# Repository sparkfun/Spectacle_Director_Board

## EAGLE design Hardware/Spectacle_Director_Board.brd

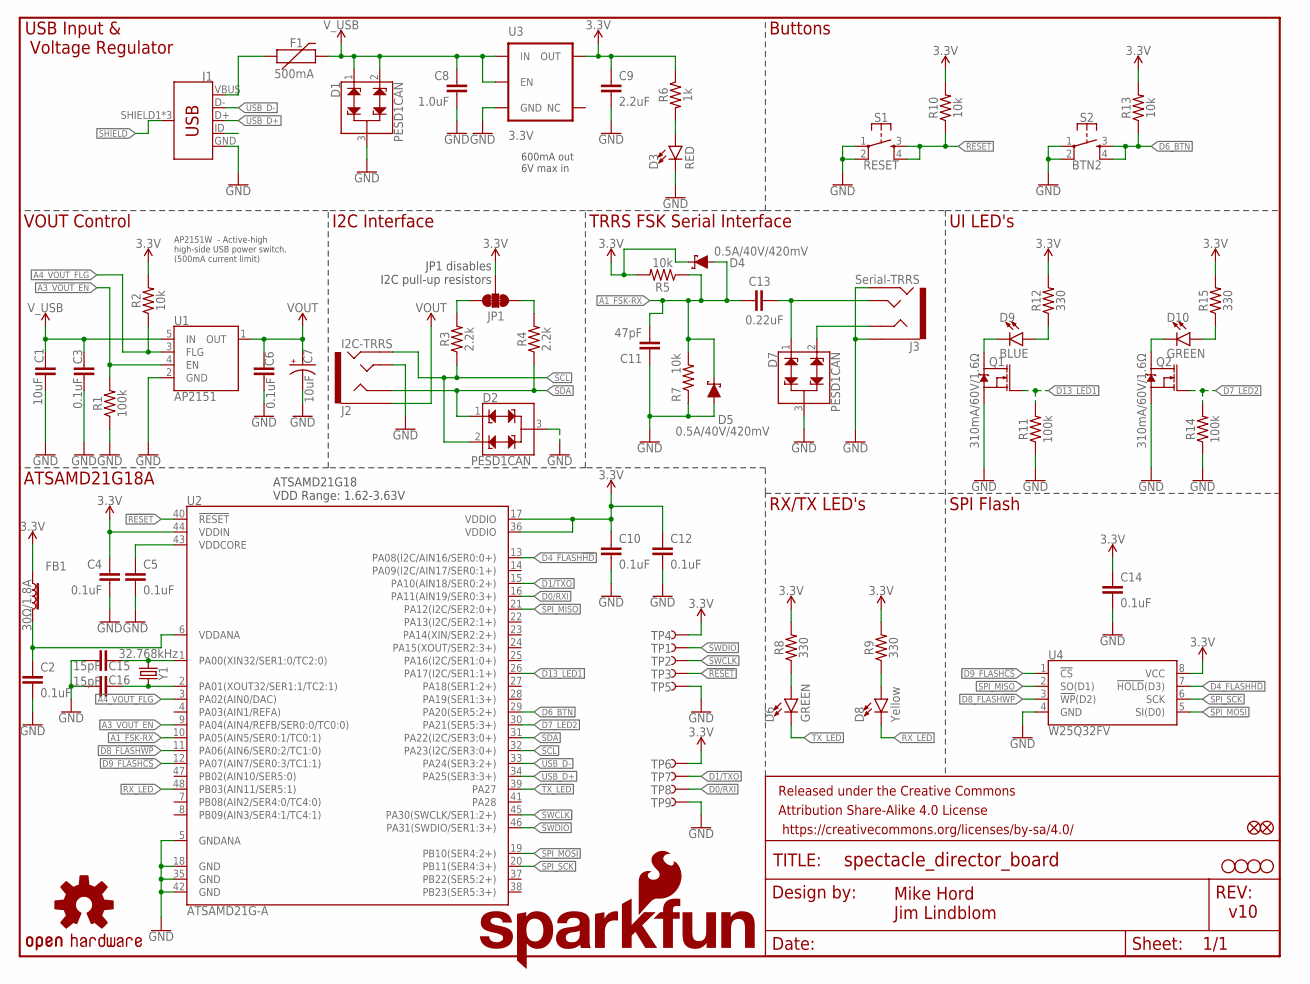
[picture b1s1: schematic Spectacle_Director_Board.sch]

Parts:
C1: 10uF; 0805
C2, C3, C4, C5, C6, C10, C12, C14: 0.1uF; 0603
C7: 10uF; EIA3216
C8: 1.0uF; 0805
C9: 2.2uF; 0603
C11: 47pF; 0603
C13: 0.22uF; 0603
C15, C16: 15pF; 0603
D1, D2, D7: PESD1CAN; SOT23-3
D3: RED; LED-0603
D4, D5: 0.5A/40V/420mV; SOD-323
D6, D10: GREEN; LED-0603
D8: Yellow; LED-0603
D9: BLUE; LED-0603
F1: 500mA; PTC-1206
FB1: 30Ω/1.8A; 0603
FD1, FD2: FIDUCIALUFIDUCIAL; FIDUCIAL-MICRO
FRAME1: FRAME-LETTER; CREATIVE_COMMONS
H1, H2, H3, H4: STAND-OFF
J1: USB_MICRO-B_FEMALE-SMT; USB-B-MICRO-SMD
J2: I2C-TRRS; AUDIO_JACK_3.5MM_TRRS_SMD_RA
J3: Serial-TRRS; AUDIO_JACK_3.5MM_TRRS_SMD_RA
JP1: JUMPER-SMT_3_2-NC_TRACE_NO-SILK; SMT-JUMPER_3_2-NC_TRACE_NO-SILK
LOGO1: OSHW-LOGOMINI; OSHW-LOGO-MINI
LOGO2: SFE_LOGO_NAME.2_INCH; SFE_LOGO_NAME_.2
LOGO3: SFE_LOGO_FLAME.1COP; SFE_LOGO_FLAME_COPPER_.1
Q1, Q2: 310mA/60V/1.6Ω; SOT323
R1, R11, R14: 100k; 0603
R2, R5, R7, R10, R13: 10k; 0603
R3, R4: 2.2k; 0603
R6: 1k; 0603
R8, R9, R12, R15: 330; 0603
S1: RESET; TACTILE_SWITCH_SMD_4.6X2.8MM
S2: BTN2; TACTILE_SWITCH_SMD_4.6X2.8MM
TP1: TP-SWDIO; PAD.03X.05
TP2: TP-SWCLK; PAD.03X.05
TP3: TP-!RESET!; PAD.03X.05
TP4: TP-3.3V; PAD.03X.05
TP5, TP6, TP7, TP8, TP9: TP-GND; PAD.03X.05
U1: AP2151; SOT23-5
U2: ATSAMD21G-A; TQFP-48
U3: 3.3V; SOT23-5
U4: W25Q32FV; SOIC-8
Y1: 32.768kHz; CRYSTAL-SMD-3.2X1.5MM

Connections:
3.3V: C4.1, C9.1, C10.1, C12.1, C14.1, D4.C, FB1.1, JP1.2, R2.2, R5.2, R6.1, R8.2, R9.2, R10.2, R12.2, R13.2, R15.2, TP4.P$1, TP6.P$1, U2.17 (VDDIO), U2.36 (VDDIO), U2.44 (VDDIN), U3.5 (OUT), U4.8 (VCC)
!RESET: R10.1, S1.3, S1.4, TP3.P$1, U2.40 (!RESET!)
A1_FSK-RX: C11.2, C13.1, D4.A, D5.C, R5.1, R7.2, U2.10 (PA05(AIN5/SER0:1/TC0:1))
A3_VOUT_EN: R1.2, U1.4 (EN), U2.9 (PA04(AIN4/REFB/SER0:0/TC0:0))
A4_VOUT_FLG: R2.1, U1.3 (FLG), U2.3 (PA02(AIN0/DAC))
D0/RXI: TP8.P$1, U2.16 (PA11(AIN19/SER0:3+))
D1/TXO: TP7.P$1, U2.15 (PA10(AIN18/SER0:2+))
D4_FLASH!HD!: U2.13 (PA08(I2C/AIN16/SER0:0+)), U4.7 (!HOLD!(D3))
D6_BTN: R13.1, S2.3, S2.4, U2.29 (PA20(SER5:2+))
D7_LED2: Q2.1 (G), R14.2, U2.30 (PA21(SER5:3+))
D8_FLASH!WP!: U2.11 (PA06(AIN6/SER0:2/TC1:0)), U4.3 (!WP!(D2))
D9_FLASH!CS!: U2.12 (PA07(AIN7/SER0:3/TC1:1)), U4.1 (!CS!)
D13_LED1: Q1.1 (G), R11.2, U2.26 (PA17(I2C/SER1:1+))
GND: C1.2, C2.2, C3.2, C4.2, C5.2, C6.2, C7.-, C8.2, C9.2, C10.2, C11.1, C12.2, C14.2, C15.1, C16.1, D1.3, D2.3, D3.C, D5.A, D7.3, J1.GND, J2.TIP, J3.EARTH, J3.RING2, Q1.2 (S), Q2.2 (S), R1.1, R7.1, R11.1, R14.1, S1.1, S1.2, S2.1, S2.2, TP5.P$1, TP9.P$1, U1.2 (GND), U2.5 (GNDANA), U2.18 (GND), U2.35 (GND), U2.42 (GND), U3.2 (GND), U4.4 (GND)
unnamed: D10.A, R15.1
unnamed: D3.A, R6.2
unnamed: C15.2, U2.1 (PA00(XIN32/SER1:0/TC2:0)), Y1.P$2 (2)
unnamed: JP1.3, R3.2
unnamed: JP1.1, R4.2
unnamed: C16.2, U2.2 (PA01(XOUT32/SER1:1/TC2:1)), Y1.P$1 (1)
unnamed: D10.C, Q2.3 (D)
unnamed: D9.A, R12.1
unnamed: D9.C, Q1.3 (D)
unnamed: D6.A, R8.1
unnamed: D8.A, R9.1
RING1-RIGHT: D7.2, J3.RING1
RX_LED: D8.C, U2.48 (PB03(AIN11/SER5:1))
SCL: D2.2, J2.RING2, R3.1, U2.32 (PA23(I2C/SER3:0+))
SDA: D2.1, J2.RING1, R4.1, U2.31 (PA22(I2C/SER3:0+))
SHIELD: J1.SHIELD1 (SHIELD), J1.SHIELD2 (SHIELD), J1.SHIELD3 (SHIELD)
SPI_MISO: U2.21 (PA12(I2C/SER2:0+)), U4.2 (SO(D1))
SPI_MOSI: U2.19 (PB10(SER4:2+)), U4.5 (SI(D0))
SPI_SCK: U2.20 (PB11(SER4:3+)), U4.6 (SCK)
SWCLK: TP2.P$1, U2.45 (PA30(SWCLK/SER1:2+))
SWDIO: TP1.P$1, U2.46 (PA31(SWDIO/SER1:3+))
TIP-LEFT: C13.2, D7.1, J3.TIP
TX_LED: D6.C, U2.39 (PA27)
USB_D+: J1.D+, U2.34 (PA25(SER3:3+))
USB_D-: J1.D-, U2.33 (PA24(SER3:2+))
USB_ID: J1.ID
VDDANA: C2.1, FB1.2, U2.6 (VDDANA)
VDDCORE: C5.1, U2.43 (VDDCORE)
VOUT: C6.1, C7.+, J2.EARTH, U1.1 (OUT)
VUSB: F1.1, J1.VBUS
V_USB: C1.1, C3.1, C8.1, D1.1, D1.2, F1.2, U1.5 (IN), U3.1 (IN), U3.3 (EN)

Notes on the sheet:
600mA out 6V max in
v10
Mike Hord Jim Lindblom
JP1 disables I2C pull-up resistors
ATSAMD21G18 VDD Range: 1.62-3.63V
USB Input & Voltage Regulator
Buttons
SPI Flash
ATSAMD21G18A
RX/TX LED's
UI LED's
I2C Interface
TRRS FSK Serial Interface
VOUT Control
AP2151W - Active-high high-side USB power switch. (500mA current limit)

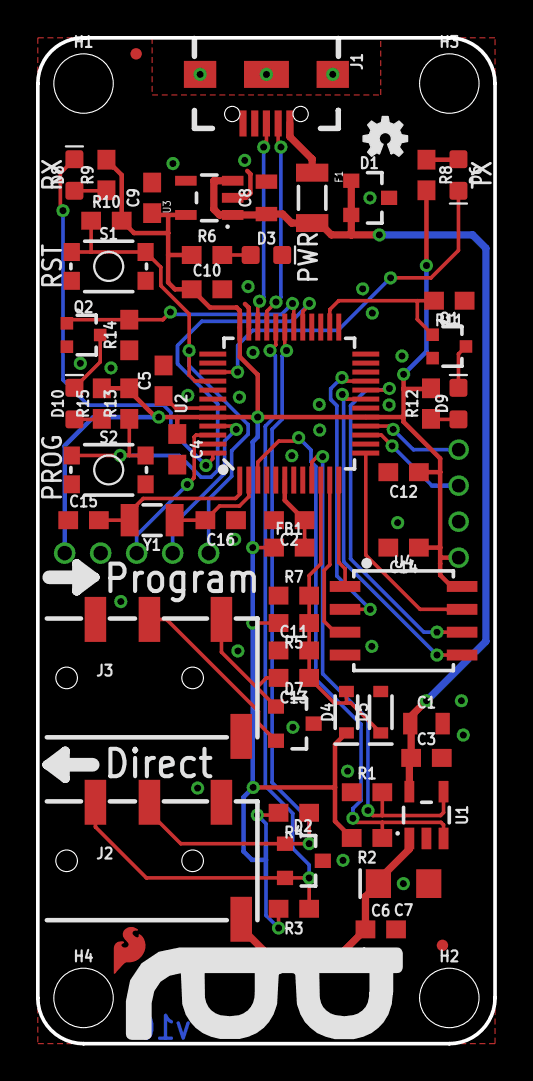
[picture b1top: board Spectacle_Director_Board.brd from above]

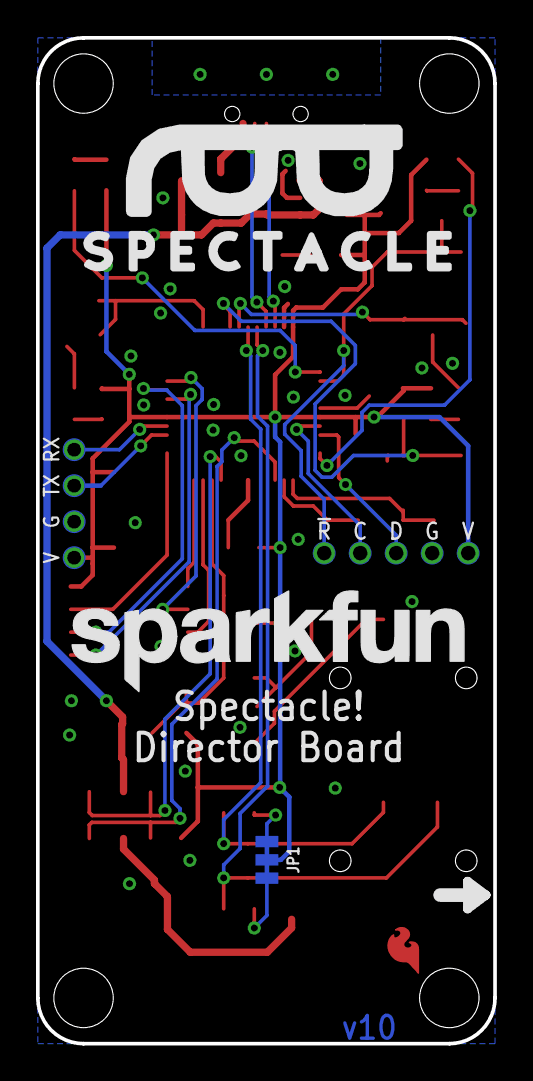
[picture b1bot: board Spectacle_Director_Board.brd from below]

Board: 2 copper layers, 25.4 x 55.9 mm, 76 parts (11 on the bottom side), 44 nets.

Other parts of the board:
U$1: ORDERING_INSTRUCTIONS

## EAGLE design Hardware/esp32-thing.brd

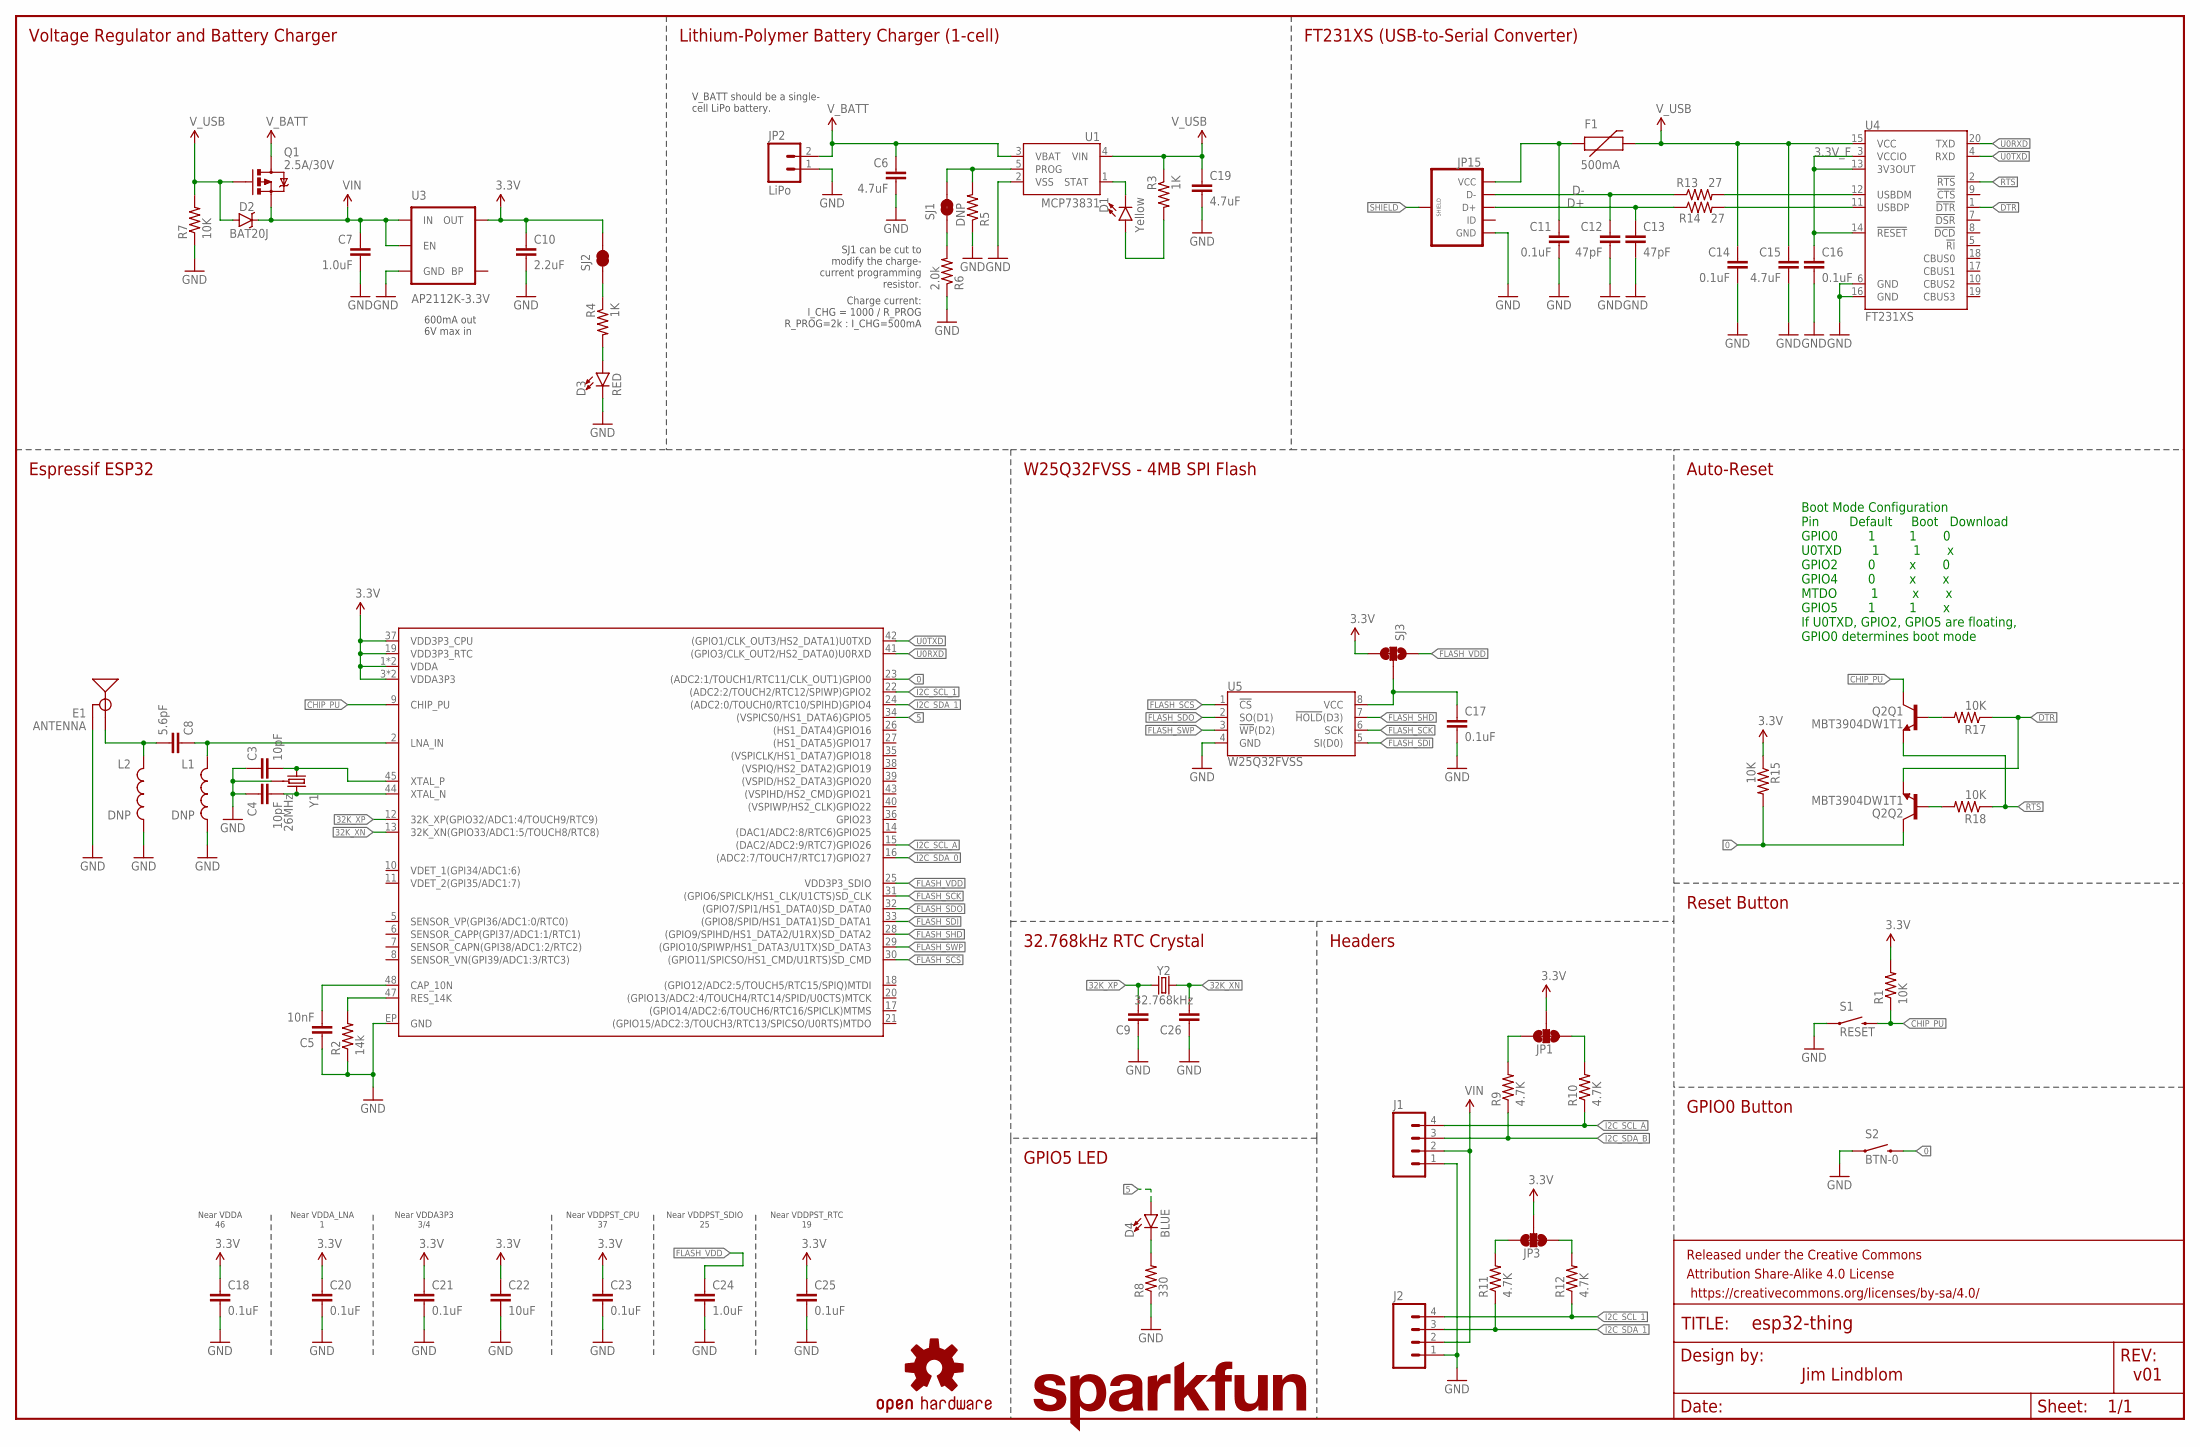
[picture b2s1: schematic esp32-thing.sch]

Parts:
C3, C4: 10pF; 0603-CAP
C5: 10nF; 0603-CAP
C6, C15, C19: 4.7uF; 0603-CAP
C7: 1.0uF; 0805-CAP
C8: 5.6pF; 0603-CAP
C9, C26: CAP0603-CAP; 0603-CAP
C10: 2.2uF; 0603-CAP
C11, C14, C16, C17, C18, C20, C21, C23, C25: 0.1uF; 0603-CAP
C12, C13: 47pF; 0603-CAP
C22: 10uF; 0603-CAP
C24: 1.0uF; 0603-CAP
D1: Yellow; LED-0603
D2: BAT20J; SOD-323
D3: RED; LED-0603
D4: BLUE; LED-0603
E1: ANTENNA; TRACE_ANTENNA_2.4GHZ_25.7MM_TUNED
F1: 500mA; PTC-1206
FRAME1: FRAME-LEDGER; CREATIVE_COMMONS
J1, J2: M04POLAR_LOCK; MOLEX-1X4_LOCK
JP1, JP3: JUMPER-PAD-3-NC_BY_TRACE; PAD-JUMPER-3-3OF3_NC_BY_TRACE_YES_SILK_FULL_BOX
JP2: LiPo; JST-2-PTH
JP15: USB_MICROB_PLUGCONN-11752; USB-B-MICRO-SMD_V03
L1, L2: DNP; 0603
LOGO1: SFE_LOGO_NAME.2_INCH; SFE_LOGO_NAME_.2
LOGO2: OSHW-LOGOMINI; OSHW-LOGO-MINI
Q1: 2.5A/30V; SOT23-3
Q2: MBT3904DW1T1; SC70-6
R1: 10K; 0603-RES
R2: 14k; 0603-RES
R3, R4: 1K; 0603-RES
R5: DNP; 1/6W-RES
R6: 2.0k; 0603-RES
R7, R15, R17, R18: 10K; 0603-RES@1
R8: 330; 0603-RES
R9, R10, R11, R12: 4.7K; 0603-RES
R13, R14: 27; 0603-RES
S1: RESET; TACTILE_SWITCH_SMD_4.6X2.8MM
S2: BTN-0; TACTILE_SWITCH_SMD_4.6X2.8MM
SJ1, SJ2: JUMPER-PAD-2-NC_BY_TRACE; PAD-JUMPER-2-NC_BY_TRACE_YES_SILK
SJ3: JUMPER-PAD-3-2OF3_NC_BY_TRACE_SMALL; PAD-JUMPER-3-2OF3_NC_BY_TRACE_YES_SILK_FULL_BOX
U1: MCP73831; SOT23-5
U3: AP2112K-3.3V; SOT23-5
U4: FT231XS; SSOP20_L
U5: W25Q32FVSS; SOIC-8
U$1: ESP32; QFN48-0.4MM
Y1: 26MHz; CRYSTAL-SMD-3.2X2.5
Y2: 32.768kHz; CRYSTAL-SMD-3.2X1.5MM

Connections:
0: Q2.6 (C), R15.2, S2.3 (2), S2.4 (2), U$1.23 ((ADC2:1/TOUCH1/RTC11/CLK_OUT1)GPIO0)
3.3V: C10.1, C18.1, C20.1, C21.1, C22.1, C23.1, C25.1, JP1.2, JP3.2, R1.2, R15.1, SJ2.2, SJ3.3, U3.5 (OUT), U$1.1 (VDDA), U$1.3 (VDDA3P3), U$1.4 (VDDA3P3), U$1.19 (VDD3P3_RTC), U$1.37 (VDD3P3_CPU), U$1.46 (VDDA)
3.3V_F: C16.1, U4.3 (VCCIO), U4.13 (3V3OUT), U4.14 (!RESET)
5: D4.A, U$1.34 ((VSPICS0/HS1_DATA6)GPIO5)
32K_XN: C26.2, U$1.13 (32K_XN(GPIO33/ADC1:5/TOUCH8/RTC8)), Y2.P$2 (2)
32K_XP: C9.2, U$1.12 (32K_XP(GPIO32/ADC1:4/TOUCH9/RTC9)), Y2.P$1 (1)
CAP_10N: C5.2, U$1.48 (CAP_10N)
CHIP_PU: Q2.3 (C), R1.1, S1.3 (2), S1.4 (2), U$1.9 (CHIP_PU)
D+: C13.1, JP15.D+, R14.1
D-: C12.1, JP15.D-, R13.1
DTR: Q2.1 (E), R17.1, U4.1 (!DTR)
FLASH_SCK: U5.6 (SCK), U$1.31 ((GPIO6/SPICLK/HS1_CLK/U1CTS)SD_CLK)
FLASH_SCS: U5.1 (!CS!), U$1.30 ((GPIO11/SPICSO/HS1_CMD/U1RTS)SD_CMD)
FLASH_SDI: U5.5 (SI(D0)), U$1.33 ((GPIO8/SPID/HS1_DATA1)SD_DATA1)
FLASH_SDO: U5.2 (SO(D1)), U$1.32 ((GPIO7/SPI1/HS1_DATA0)SD_DATA0)
FLASH_SHD: U5.7 (!HOLD!(D3)), U$1.28 ((GPIO9/SPIHD/HS1_DATA2/U1RX)SD_DATA2)
FLASH_SWP: U5.3 (!WP!(D2)), U$1.29 ((GPIO10/SPIWP/HS1_DATA3/U1TX)SD_DATA3)
FLASH_VDD: C24.1, SJ3.1, U$1.25 (VDD3P3_SDIO)
GND: C3.1, C4.1, C5.1, C6.2, C7.2, C9.1, C10.2, C11.2, C12.2, C13.2, C14.2, C15.2, C16.2, C17.2, C18.2, C19.2, C20.2, C21.2, C22.2, C23.2, C24.2, C25.2, C26.1, D3.C, E1.GND, E1.GND2 (GND), J1.1, J2.1, JP2.1, JP15.GND, L1.2, L2.2, R2.1, R5.1, R6.1, R7.1, R8.1, S1.1, S1.2 (1), S2.1, S2.2 (1), U1.2 (VSS), U3.2 (GND), U4.6 (GND), U4.16 (GND), U5.4 (GND), U$1.EP (GND), Y1.2 (GND), Y1.4 (GND)
I2C_SCL_1: J2.4, R12.1, U$1.22 ((ADC2:2/TOUCH2/RTC12/SPIWP)GPIO2)
I2C_SCL_A: J1.4, R10.1, U$1.15 ((DAC2/ADC2:9/RTC7)GPIO26)
I2C_SDA_0: U$1.16 ((ADC2:7/TOUCH7/RTC17)GPIO27)
I2C_SDA_1: J2.3, R11.1, U$1.24 ((ADC2:0/TOUCH0/RTC10/SPIHD)GPIO4)
I2C_SDA_B: J1.3, R9.1
LNA_IN: C8.1, L1.1, U$1.2 (LNA_IN)
unnamed: D4.C, R8.2
unnamed: D3.A, R4.2
unnamed: R4.1, SJ2.1
unnamed: JP3.3, R11.2
unnamed: JP3.1, R12.2
unnamed: JP1.3, R9.2
unnamed: R13.2, U4.12 (USBDM)
unnamed: R14.2, U4.11 (USBDP)
unnamed: D1.C, U1.1 (STAT)
unnamed: Q2.5 (B), R17.2
unnamed: JP1.1, R10.2
unnamed: Q2.2 (B), R18.2
unnamed: R5.2, SJ1.2, U1.5 (PROG)
unnamed: R6.2, SJ1.1
unnamed: D1.A, R3.2
RES_14K: R2.2, U$1.47 (RES_14K)
RTS: Q2.4 (E), R18.1, U4.2 (!RTS)
SHIELD: JP15.SHIELD1 (SHIELD), JP15.SHIELD2 (SHIELD), JP15.SHIELD3 (SHIELD)
TRACE_ANT: C8.2, E1.ANT (SIGNAL), L2.1
U0RXD: U4.20 (TXD), U$1.41 ((GPIO3/CLK_OUT2/HS2_DATA0)U0RXD)
U0TXD: U4.4 (RXD), U$1.42 ((GPIO1/CLK_OUT3/HS2_DATA1)U0TXD)
VCC_FLASH: C17.1, SJ3.2, U5.8 (VCC)
VIN: C7.1, D2.C, J1.2, J2.2, Q1.2 (S), U3.1 (IN), U3.3 (EN)
VUSB: C11.1, F1.1, JP15.VBUS (VCC)
V_BATT: C6.1, JP2.2, Q1.3 (D), U1.3 (VBAT)
V_USB: C14.1, C15.1, C19.1, D2.A, F1.2, Q1.1 (G), R3.1, R7.2, U1.4 (VIN), U4.15 (VCC)
XTAL_N_: C4.2, U$1.44 (XTAL_N), Y1.3 (2)
XTAL_P_: C3.2, U$1.45 (XTAL_P), Y1.1

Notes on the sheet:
Boot Mode Configuration Pin Default Boot Download GPIO0 1 1 0 U0TXD 1 1 x GPIO2 0 x 0 GPIO4 0 x x MTDO 1 x x GPIO5 1 1 x If U0TXD, GPIO2, GPIO5 are floating, GPIO0 determines boot mode
FT231XS (USB-to-Serial Converter)
V_BATT should be a single- cell LiPo battery.
Charge current: I_CHG = 1000 / R_PROG R_PROG=2k : I_CHG=500mA
Voltage Regulator and Battery Charger
SJ1 can be cut to modify the charge- current programming resistor.
Lithium-Polymer Battery Charger (1-cell)
600mA out 6V max in
Auto-Reset
Near VDDA 46
Near VDDA_LNA 1
Near VDDA3P3 3/4
Near VDDPST_CPU 37
Near VDDPST_SDIO 25
Near VDDPST_RTC 19
Espressif ESP32
W25Q32FVSS - 4MB SPI Flash
32.768kHz RTC Crystal
GPIO0 Button
Reset Button
GPIO5 LED
Headers
v01
Jim Lindblom

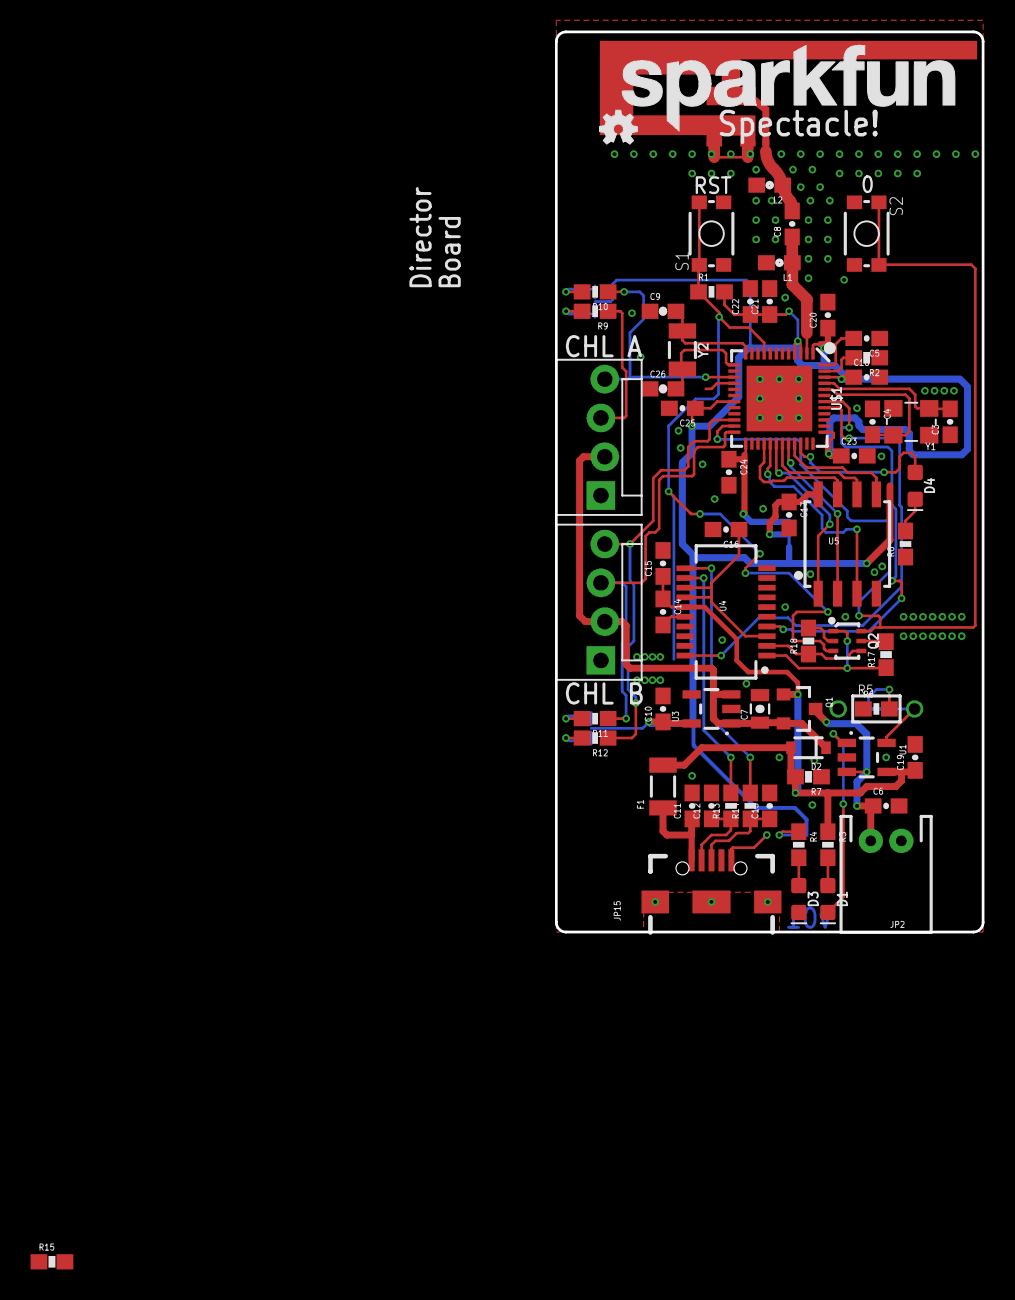
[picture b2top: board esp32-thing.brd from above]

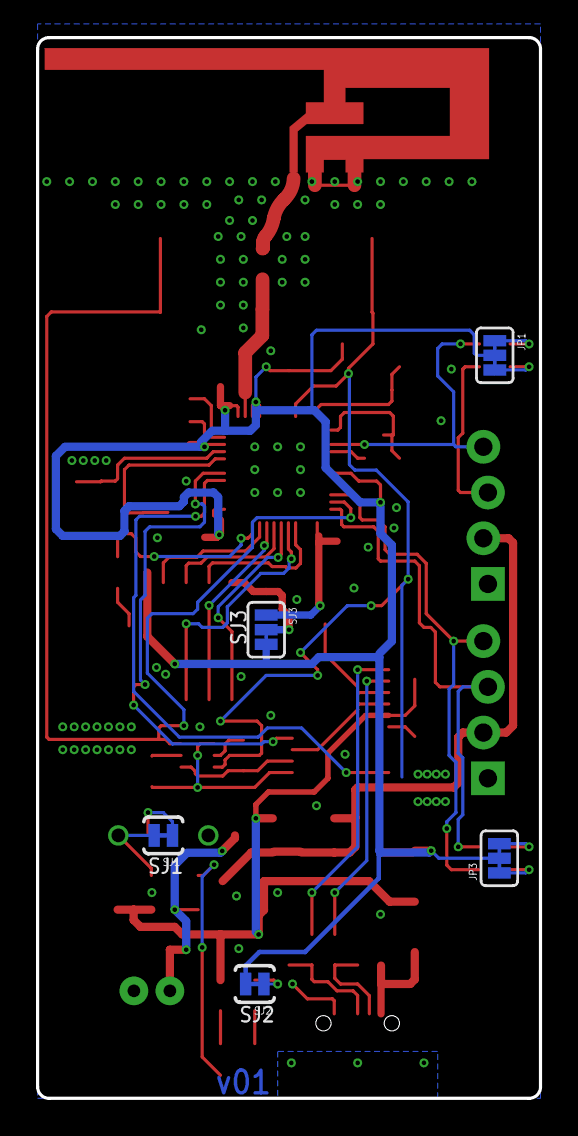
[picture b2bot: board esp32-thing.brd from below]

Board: 2 copper layers, 27.9 x 58.9 mm, 72 parts (5 on the bottom side), 52 nets.

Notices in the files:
parts and their libraries:
SparkFun-Resistors: Licensing: Creative Commons ShareAlike 4.0 International - https://creativecommons.org/licenses/by-sa/4.0
SparkFun-Aesthetics: Released under the Creative Commons Attribution Share-Alike 4.0 License
SparkFun-Aesthetics: https://creativecommons.org/licenses/by-sa/4.0
